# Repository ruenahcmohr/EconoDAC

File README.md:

# EconoDAC

This is an 8 bit, serial, modified R-2R DAC using the 74HC595.

Enjoy.

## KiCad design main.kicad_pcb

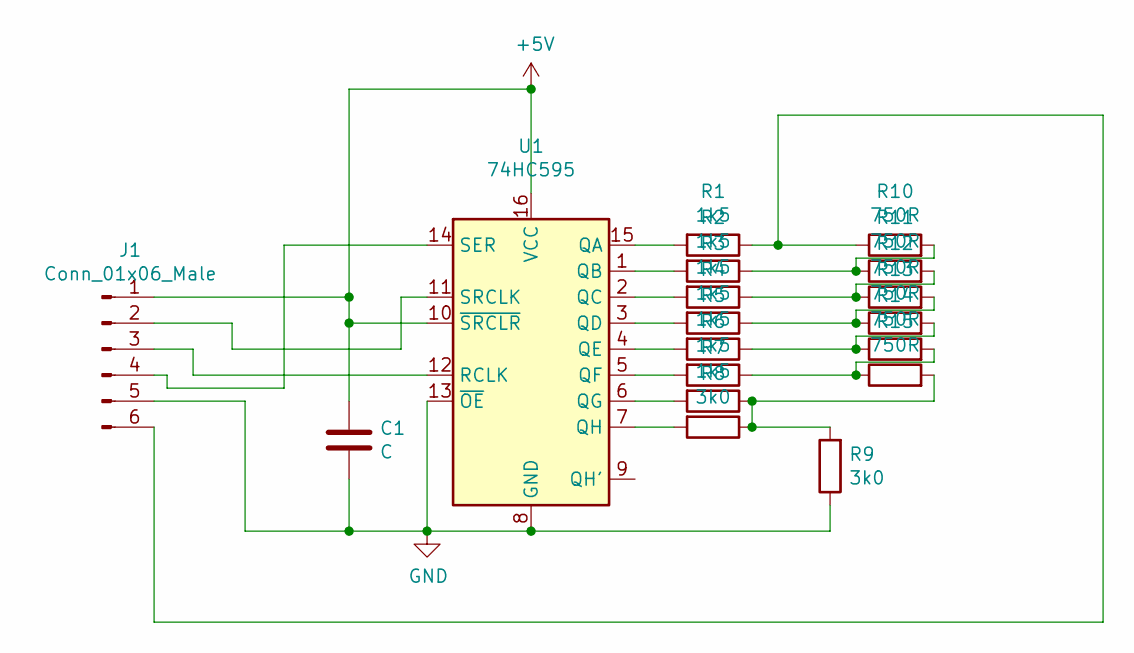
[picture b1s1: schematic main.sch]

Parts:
C1: C; C_0805_2012Metric_Pad1.15x1.40mm_HandSolder
J1: Conn_01x06_Male; PinHeader_1x06_P2.54mm_Vertical
R1, R2, R3, R4, R5, R6, R7: 1k5; R_0805_2012Metric_Pad1.15x1.40mm_HandSolder
R8, R9: 3k0; R_0805_2012Metric_Pad1.15x1.40mm_HandSolder
R10, R11, R12, R13, R14, R15: 750R; R_0805_2012Metric_Pad1.15x1.40mm_HandSolder
U1: 74HC595; SOIC-16_3.9x9.9mm_P1.27mm

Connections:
+5V: C1.1, J1.1, U1.10 (~SRCLR), U1.16 (VCC)
GND: C1.2, J1.5, R9.1, U1.8 (GND), U1.13 (~OE)
unnamed: J1.2, U1.11 (SRCLK)
unnamed: J1.3, U1.12 (RCLK)
unnamed: J1.4, U1.14 (SER)
unnamed: J1.6, R1.1, R10.1
unnamed: R1.2, U1.15 (QA)
unnamed: R2.2, U1.1 (QB)
unnamed: R3.2, U1.2 (QC)
unnamed: R4.2, U1.3 (QD)
unnamed: R5.2, U1.4 (QE)
unnamed: R6.2, U1.5 (QF)
unnamed: R7.2, U1.6 (QG)
unnamed: R8.2, U1.7 (QH)
unnamed: R2.1, R10.2, R11.1
unnamed: R3.1, R11.2, R12.1
unnamed: R4.1, R12.2, R13.1
unnamed: R5.1, R13.2, R14.1
unnamed: R6.1, R14.2, R15.1
unnamed: R7.1, R8.1, R9.2, R15.2

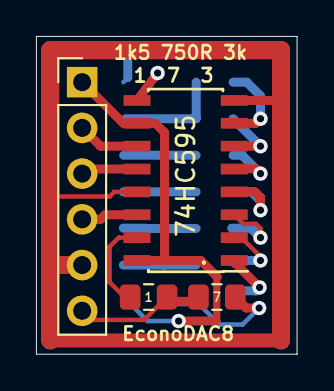
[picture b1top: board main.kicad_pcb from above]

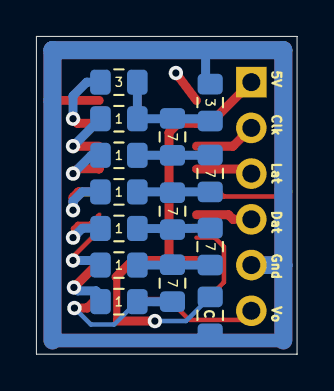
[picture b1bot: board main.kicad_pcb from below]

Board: 2 copper layers, 14.5 x 17.7 mm, 18 parts (14 on the bottom side), 20 nets.
